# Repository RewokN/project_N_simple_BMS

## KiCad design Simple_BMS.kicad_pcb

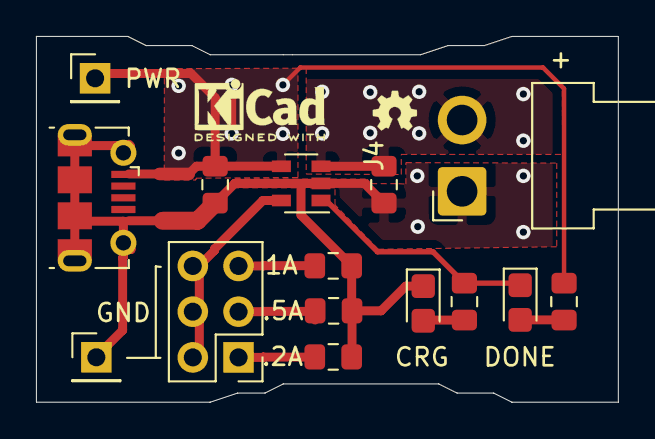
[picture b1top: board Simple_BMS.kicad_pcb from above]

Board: 2 copper layers, 32.3 x 20.3 mm, 15 parts (0 on the bottom side), 10 nets.

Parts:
C1, C2: 10uF; C_0805_2012Metric_Pad1.15x1.40mm_HandSolder
D1: Red; LED_0805_2012Metric_Castellated
D2: Green; LED_0805_2012Metric_Castellated
J1: USB_B_Micro; USB_Micro-B_Molex-105017-0001
J2, J5: Conn_01x01; PinHeader_1x01_P2.54mm_Vertical
J3: Conn_02x03_Odd_Even; PinHeader_2x03_P2.54mm_Vertical
J4: Conn_01x02; JST_VH_B2PS-VH_1x02_P3.96mm_Horizontal
R1, R2: 470R; R_0805_2012Metric_Pad1.15x1.40mm_HandSolder
R3: 1K; R_0805_2012Metric_Pad1.15x1.40mm_HandSolder
R4: 2K; R_0805_2012Metric_Pad1.15x1.40mm_HandSolder
R5: 5K; R_0805_2012Metric_Pad1.15x1.40mm_HandSolder
U1: MCP73831-5-OT; SOT-23-5

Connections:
GNDREF: C1.2, C2.2, D2.1, J1.5, J1.6, J4.1, J5.1, R3.2, R4.2, R5.2, U1.2
unnamed: C1.1, J1.1, J2.1, R1.2, U1.4
unnamed: C2.1, J4.2, U1.3
unnamed: D1.1, R2.1, U1.1
unnamed: D1.2, R1.1
unnamed: D2.2, R2.2
unnamed: J3.1, R3.1
unnamed: J3.2, J3.4, J3.6, U1.5
unnamed: J3.3, R4.1
unnamed: J3.5, R5.1
